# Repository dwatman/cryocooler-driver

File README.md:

# cryocooler-driver
Driver circuit for a small Stirling-cycle cryocooler

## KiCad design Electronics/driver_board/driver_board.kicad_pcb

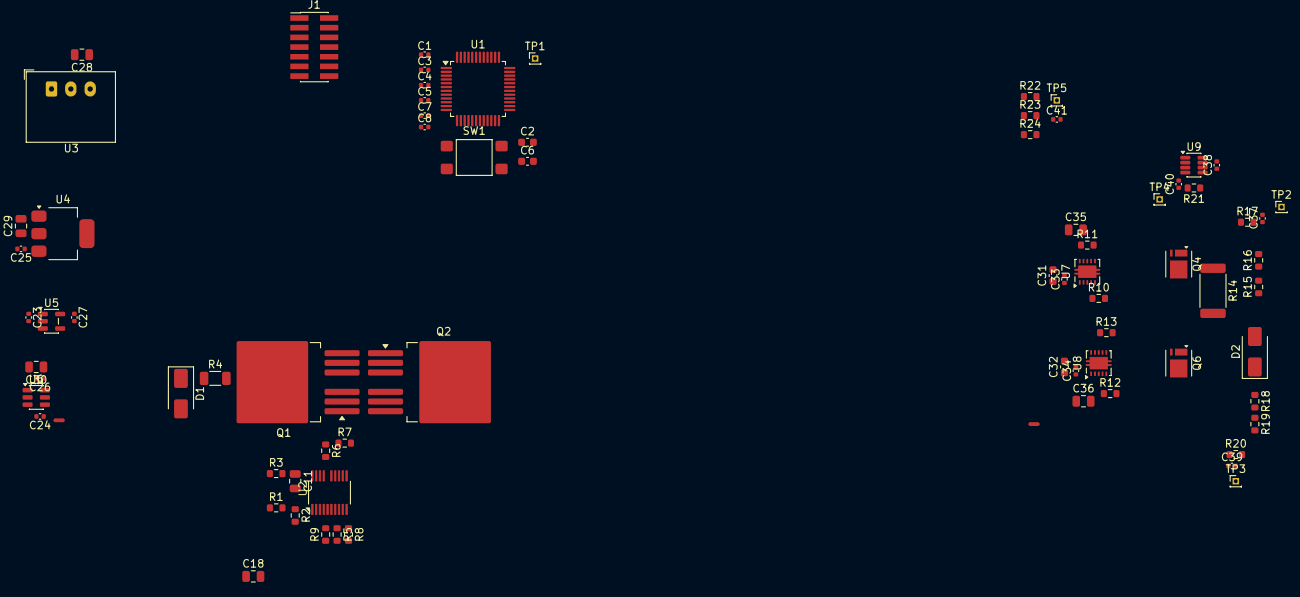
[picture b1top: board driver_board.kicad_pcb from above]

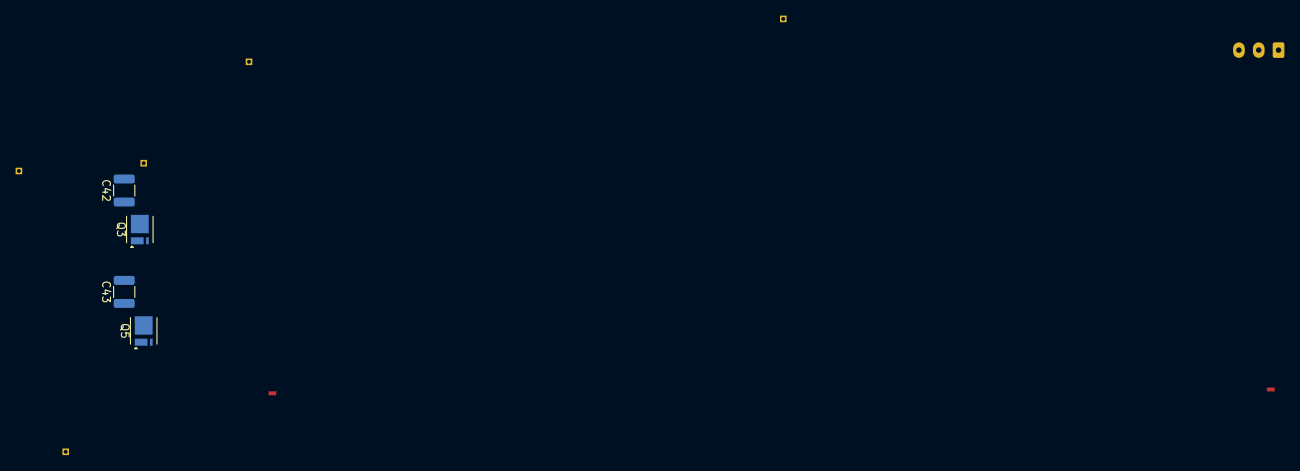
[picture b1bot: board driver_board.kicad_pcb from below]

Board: 4 copper layers, 81 parts (4 on the bottom side), 54 nets, no tracks yet.

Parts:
C1, C3, C4, C5, C7, C8, C24, C25, C26, C33, C34, C37, C38, C39, C40, C41: 0.1u; C_0402_1005Metric
C2, C6, C31, C32: 4.7u; C_0603_1608Metric
C11, C18, C35, C36: 0.1u 150V; C_0805_2012Metric
C23, C27: 1u; C_0402_1005Metric
C28, C29, C30: 10u; C_0805_2012Metric
C42, C43: 0.47u 200V; C_1210_3225Metric
D1: SMAJ85A; D_SMA
D2: SMAJ100CA; D_SMA
J1: Conn_ST_STDC14; PinHeader_2x07_P1.27mm_Vertical_SMD
NT1, NT2: NetTie_2; NetTie-2_SMD_Pad0.5mm
Q1, Q2: IPF036N15NM6; TO-263-6
Q3, Q4, Q5, Q6: IAUZ40N10S5N130; Infineon_PG-TSDSON-8-33
R1: 150k; R_0603_1608Metric
R2, R9: 11k; R_0603_1608Metric
R3, R21: 100R; R_0603_1608Metric
R4: 2m; R_1206_3216Metric
R5: 4.7k; R_0603_1608Metric
R6, R8: 100k; R_0603_1608Metric
R7: 10R; R_0603_1608Metric
R10, R11, R12, R13: 4.7R; R_0603_1608Metric
R14: 7m; R_2512_6332Metric
R15, R18, R22: 267k; R_0603_1608Metric
R16, R19, R23: 10k; R_0603_1608Metric
R17, R20, R24: 1k; R_0603_1608Metric
SW1: TL3305; SW_Push_1P1T_NO_E-Switch_TL3305AFxxxQG
TP1, TP2, TP3, TP4, TP5: TestPoint; PinHeader_1x01_P1.00mm_Vertical
U1: STM32G491CCT6; LQFP-48_7x7mm_P0.5mm
U2: TPS4810-Q1; TI_VSSOP-19_3x5.1mm_P0.5mm
U3: LMW78_12-0.5R; Converter_DCDC_GAPTEC_LMW78_THT
U4: LD1117S50CTR; SOT-223-3_TabPin2
U5: LD39015M33R; SOT-23-5
U6: REF3433TIDBVR; SOT-23-6
U7, U8: UCC27302ADRCR; TI_VSON-10-1EP_3x3mm_P0.5mm_EP1.65x2.4mm
U9: INA241A2xDDF; SOT-23-8

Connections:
+3.3V: C2.1, C3.1, C4.1, C5.1, C27.1, J1.3 (VCC), R9.1, U1.1 (VBAT), U1.24 (VDD), U1.36 (VDD), U1.48 (VDD), U5.5 (OUT)
+3.3VA: C6.1, C7.1, C8.1, C26.1, C30.1, C38.1, U1.20 (VREF+), U1.21 (VDDA), U6.6 (VREF), U9.6 (V+), U9.7 (REF1)
+5V: C23.1, C24.1, C29.1, U4.2 (VO), U5.1 (IN), U5.3 (EN), U6.4 (VIN)
+12V: C25.1, C28.1, C31.1, C32.1, C33.1, C34.1, U3.3 (OUT), U4.3 (VI), U7.1 (VDD), U8.1 (VDD)
+VDC: C42.1, C43.1, Q2.4 (D), Q3.3 (D), Q5.3 (D), R22.1
/RSTN: C1.1, J1.12 (~RST), SW1.2, U1.7 (PG10-NRST)
/SWCLK: J1.6 (JCLK/SWCLK), U1.38 (SWCLK-JTCK)
/SWDIO: J1.4 (JTMS/SWDIO), U1.37 (SWDIO-JTMS)
/SWO: J1.8 (JTDO/SWO), U1.40 (TRACESWO)
/VCP_RX: J1.13 (VCP_RX), U1.44 (USART1_RX)
/VCP_TX: J1.14 (VCP_TX), U1.43 (USART1_TX)
/hbridge/COIL_A: D2.2 (A2), R14.2, R15.1, U9.1 (-)
/hbridge/COIL_A2: C35.2, Q3.1 (S), Q4.3 (D), R14.1, U7.5 (HS), U9.8 (+)
/hbridge/COIL_B: C36.2, D2.1 (A1), Q5.1 (S), Q6.3 (D), R18.1, U8.5 (HS)
/power/PWR_EN: U2.2 (INP2), U2.3 (INP1)
/power/PWR_FLT: R9.2, U2.5 (FLT)
/power/VIN: D1.1 (A1), R1.1, R3.1, R4.1, U2.18 (CS+)
GND: C1.2, C2.2, C3.2, C4.2, C5.2, C23.2, C24.2, C25.2, C27.2, C29.2, J1.5 (GND), J1.7 (GND), J1.11 (GNDDetect), NT1.1, NT2.1, SW1.1, U1.23 (VSS), U1.35 (VSS), U1.47 (VSS), U4.1 (GND), U5.2 (GND)
GNDA: C6.2, C7.2, C8.2, C26.2, C30.2, C37.2, C38.2, C39.2, C40.2, C41.2, NT1.2, R16.2, R19.2, R23.2, U1.19 (VSSA), U6.2 (GND), U9.2 (GND), U9.3 (REF2), U9.4 (GND)
GNDP: C11.2, C31.2, C32.2, C33.2, C34.2, C42.2, C43.2, D1.2 (A2), NT2.2, Q4.1 (S), Q6.1 (S), R2.2, R5.2, R8.2, U2.6 (GND), U2.7 (CS_SEL), U2.10 (SCP_TEST), U7.9 (VSS), U7.11 (PAD), U8.9 (VSS), U8.11 (PAD)
HBRIDGE_AH: U1.30 (TIM1_CH1), U7.7 (HI)
HBRIDGE_AL: U1.33 (TIM1_CH1N), U7.8 (LI)
HBRIDGE_BH: U1.34 (TIM1_CH2N), U8.7 (HI)
HBRIDGE_BL: U1.31 (TIM1_CH2), U8.8 (LI)
HBRIDGE_EN: U7.6 (EN), U8.6 (EN)
Isense: C40.1, R21.2, TP4.1, U1.17 (ADC3_IN1)
unnamed: Q1.4 (D), R4.2, U2.17 (CS-)
unnamed: Q1.1 (G), R6.1, R7.1, U2.14 (G1PD)
unnamed: Q1.2 (S), Q1.3 (S), Q1.5 (S), Q1.6 (S), Q1.7 (S), Q2.2 (S), Q2.3 (S), Q2.5 (S), Q2.6 (S), Q2.7 (S)
unnamed: Q2.1 (G), U2.11 (G2)
unnamed: Q3.2 (G), R10.2
unnamed: Q4.2 (G), R11.2
unnamed: Q5.2 (G), R12.2
unnamed: Q6.2 (G), R13.2
unnamed: R15.2, R16.1, R17.1
unnamed: R18.2, R19.1, R20.1
unnamed: R21.1, U9.5
unnamed: R22.2, R23.1, R24.1
unnamed: TP1.1, U1.32 (TIM1_CH3)
unnamed: R1.2, R2.1, U2.1 (EN/UVLO)
unnamed: R6.2, U2.15 (G1PU)
unnamed: R5.1, U2.8 (ISCP)
unnamed: R8.1, U2.9 (TMR)
unnamed: C11.1, R3.2, U2.20 (VS)
unnamed: C28.2, U3.2 (GND)
unnamed: C35.1, U7.3 (HB)
unnamed: R10.1, U7.4 (HO)
unnamed: R11.1, U7.10 (LO)
unnamed: C36.1, U8.3 (HB)
unnamed: R12.1, U8.4 (HO)
unnamed: R13.1, U8.10 (LO)
Vsense_A: C37.1, R17.2, TP2.1, U1.8 (ADC12_IN1)
Vsense_B: C39.1, R20.2, TP3.1, U1.9 (ADC12_IN2)
Vsense_bus: C41.1, R24.2, TP5.1, U1.27 (ADC3_IN5)

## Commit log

2025-12-30 [pcb] Added KiCad library as submodule
2025-12-30 [stm32] Added initial .ioc
2025-12-31 [pcb] Created PCB project
2026-01-01 [pcb] Added MCU, current sense parts
2026-01-03 Added H-bridge
2026-01-03 [pcb] Added HV DC-DC converter
2026-01-04 [pcb] Added more power supply parts, split power to separate sheet
2026-01-05 [pcb] Separated H-bridge to new sheet
2026-01-06 [mcu] Changed to correct device footprint
2026-01-06 [pcb] Added regulators, pin mapping
2026-01-07 [pcb] Populating efuse parts
2026-01-15 Added TVS diodes, bulk capacitors
2026-01-15 Initial PCB configuration
2026-01-15 Initial placement
2026-01-21 Added more capacitors, part numbers.
